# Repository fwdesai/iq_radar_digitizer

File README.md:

IQ radar digitizer board for vital signs monitoring

v1

v2

v2 board pictured with K-LC5 mm-wave singled ended module:

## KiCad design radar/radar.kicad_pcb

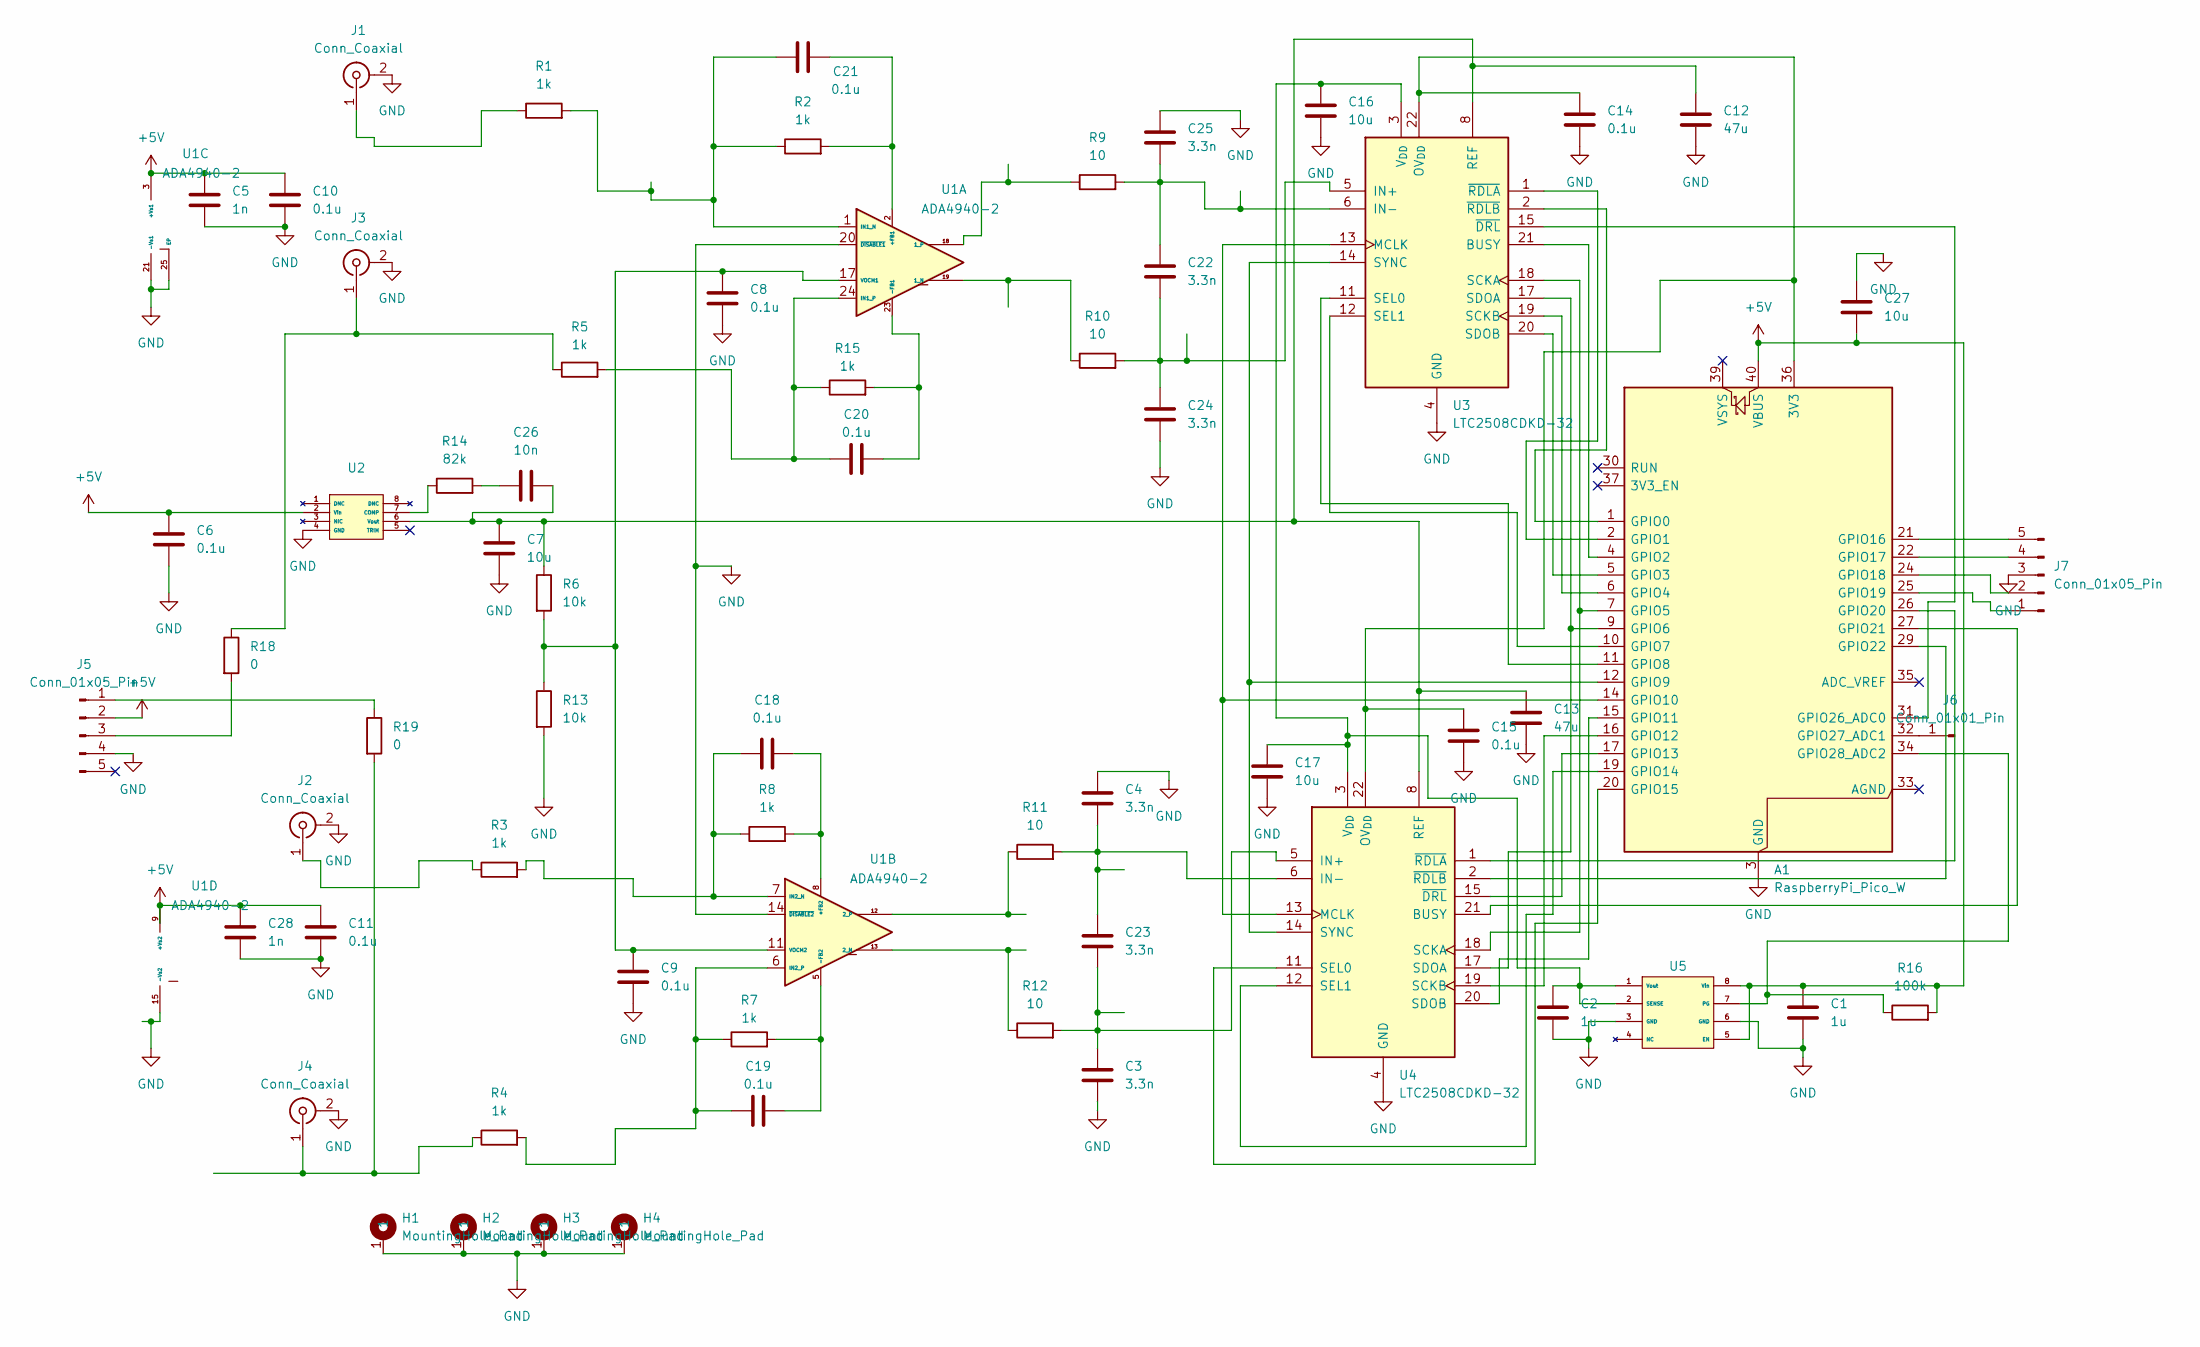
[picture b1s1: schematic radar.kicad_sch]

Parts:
A1: RaspberryPi_Pico_W; RaspberryPi_Pico_Common_THT
C1, C2: 1u; C_0603_1608Metric
C3, C4, C22, C23, C24, C25: 3.3n; C_0603_1608Metric
C5, C28: 1n; C_0603_1608Metric
C6, C8, C9, C10, C11, C14, C15, C18, C19, C20, C21: 0.1u; C_0603_1608Metric
C7, C16, C17, C27: 10u; C_0603_1608Metric
C12, C13: 47u; C_1210_3225Metric_Pad1.33x2.70mm_HandSolder
C26: 10n; C_0603_1608Metric
H1, H2, H3, H4: MountingHole_Pad; MountingHole_4.3mm_M4_Pad_Via
J1, J2, J3, J4: Conn_Coaxial; SMA_Amphenol_132289_EdgeMount
J5: Conn_01x05_Pin; PinHeader_1x05_P2.54mm_Horizontal
J6: Conn_01x01_Pin; PinHeader_1x01_P2.54mm_Vertical
J7: Conn_01x05_Pin; PinHeader_1x05_P2.54mm_Vertical
R1, R2, R3, R4, R5, R7, R8, R15: 1k; R_0603_1608Metric
R6, R13: 10k; R_0603_1608Metric
R9, R10, R11, R12: 10; R_0603_1608Metric
R14: 82k; R_0603_1608Metric
R16: 100k; R_0603_1608Metric
R18, R19: 0; R_0603_1608Metric
U1: ADA4940-2; LFCSP-24-1EP_4x4mm_P0.5mm_EP2.5x2.5mm_ThermalVias
U2: SOIC-8_3.9x4.9mm_P1.27mm
U3, U4: LTC2508CDKD-32; DFN-24-1EP_4x7mm_P0.5mm_EP2.64x6.44mm
U5: SOIC-8-1EP_3.9x4.9mm_P1.27mm_EP2.29x3mm

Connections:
+5V: A1.40 (VBUS), C1.1, C5.1, C6.1, C10.1, C11.1, C27.2, C28.1, J5.2, R16.2, U1.3 (+Vs1), U1.4 (+FB2), U1.9 (+Vs2), U1.10 (+FB2), U2.2 (Vin), U5.5 (EN), U5.8 (Vin)
unnamed: A1.36 (3V3), C14.1, C15.1, U3.22 (OV_{DD}), U4.22 (OV_{DD})
unnamed: A1.1 (GPIO0), U3.2 (~RDLB)
unnamed: A1.2 (GPIO1), U3.1 (~RDLA)
unnamed: A1.4 (GPIO2), U3.21 (BUSY)
unnamed: A1.5 (GPIO3), U3.20 (SDOB)
unnamed: A1.6 (GPIO4), U3.19 (SCKB)
unnamed: A1.7 (GPIO5), U3.18 (SCKA), U4.18 (SCKA)
unnamed: A1.9 (GPIO6), U3.17 (SDOA), U4.17 (SDOA)
unnamed: A1.10 (GPIO7), U3.12 (SEL1)
unnamed: A1.11 (GPIO8), U3.11 (SEL0)
unnamed: A1.12 (GPIO9), U3.14 (SYNC), U4.14 (SYNC)
unnamed: A1.14 (GPIO10), U3.13 (MCLK), U4.13 (MCLK)
unnamed: A1.15 (GPIO11), U4.20 (SDOB)
unnamed: A1.16 (GPIO12), U4.19 (SCKB)
unnamed: A1.17 (GPIO13), U4.15 (~DRL)
unnamed: A1.19 (GPIO14), U4.12 (SEL1)
unnamed: A1.20 (GPIO15), U4.11 (SEL0)
unnamed: A1.21 (GPIO16), J7.5
unnamed: A1.22 (GPIO17), J7.4
unnamed: A1.24 (GPIO18), J7.2
unnamed: A1.25 (GPIO19), J7.1
unnamed: A1.26 (GPIO20), U4.1 (~RDLA)
unnamed: A1.27 (GPIO21), U4.21 (BUSY)
unnamed: A1.31 (GPIO26_ADC0), U3.15 (~DRL)
unnamed: A1.32 (GPIO27_ADC1), J6.1
unnamed: A1.34 (GPIO28_ADC2), R16.1, U5.7 (PG)
unnamed: C26.1, R14.2
unnamed: J1.1 (In-), R1.1
unnamed: J2.1 (In), R3.1
unnamed: J3.1 (In+), R5.1, R18.1
unnamed: J4.1 (In), R4.1, R19.2
unnamed: J5.1, R19.1
unnamed: J5.3, R18.2
unnamed: R10.1, U1.19 (1_N)
unnamed: R9.1, U1.18 (1_P)
unnamed: C21.2, R2.2, U1.2 (+FB1)
unnamed: C20.2, R15.2, U1.23 (-FB1)
unnamed: C21.1, R1.2, R2.1, U1.1 (IN1_N)
unnamed: C20.1, R5.2, R15.1, U1.24 (IN1_P)
unnamed: C8.1, C9.1, R6.2, R13.1, U1.11 (VOCM2), U1.17 (VOCM1)
unnamed: R12.1, U1.13 (2_N)
unnamed: R11.1, U1.12 (2_P)
unnamed: C18.2, R8.2, U1.8 (+FB2)
unnamed: C19.2, R7.2, U1.5 (-FB2)
unnamed: C18.1, R3.2, R8.1, U1.7 (IN2_N)
unnamed: C19.1, R4.2, R7.1, U1.6 (IN2_P)
unnamed: R14.1, U2.7 (COMP)
unnamed: C7.1, C12.1, C13.1, C26.2, R6.1, U2.6 (Vout), U3.8 (REF), U3.9 (REF), U3.10 (REF), U4.8 (REF), U4.9 (REF), U4.10 (REF)
unnamed: C22.2, C24.1, R10.2, U3.5 (IN+)
unnamed: C22.1, C25.2, R9.2, U3.6 (IN-)
unnamed: C2.1, C16.1, C17.1, U3.3 (V_{DD}), U4.3 (V_{DD}), U5.1 (Vout), U5.2 (SENSE)
unnamed: C3.1, C23.2, R12.2, U4.5 (IN+)
unnamed: C4.2, C23.1, R11.2, U4.6 (IN-)

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
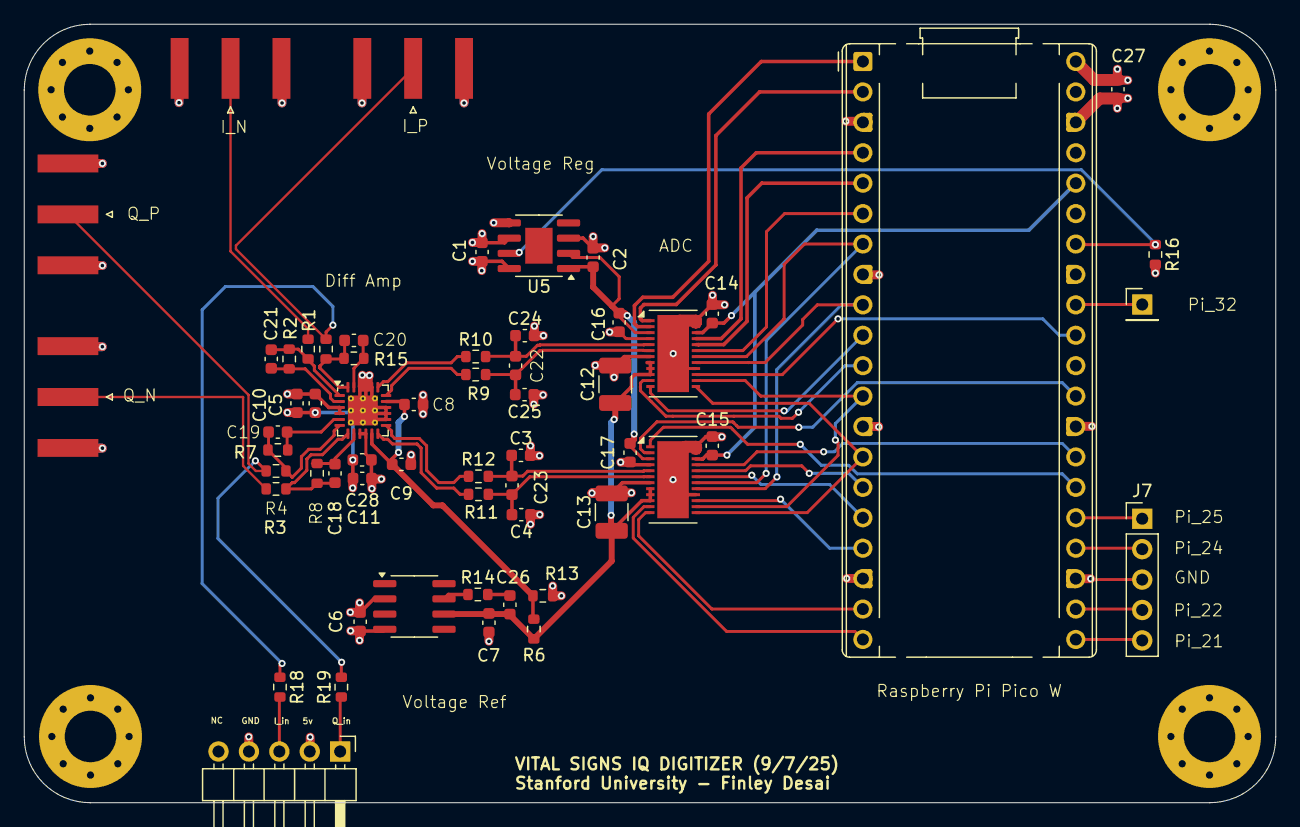
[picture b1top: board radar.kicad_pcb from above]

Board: 4 copper layers, 104.5 x 65.0 mm, 63 parts (0 on the bottom side), 56 nets.
